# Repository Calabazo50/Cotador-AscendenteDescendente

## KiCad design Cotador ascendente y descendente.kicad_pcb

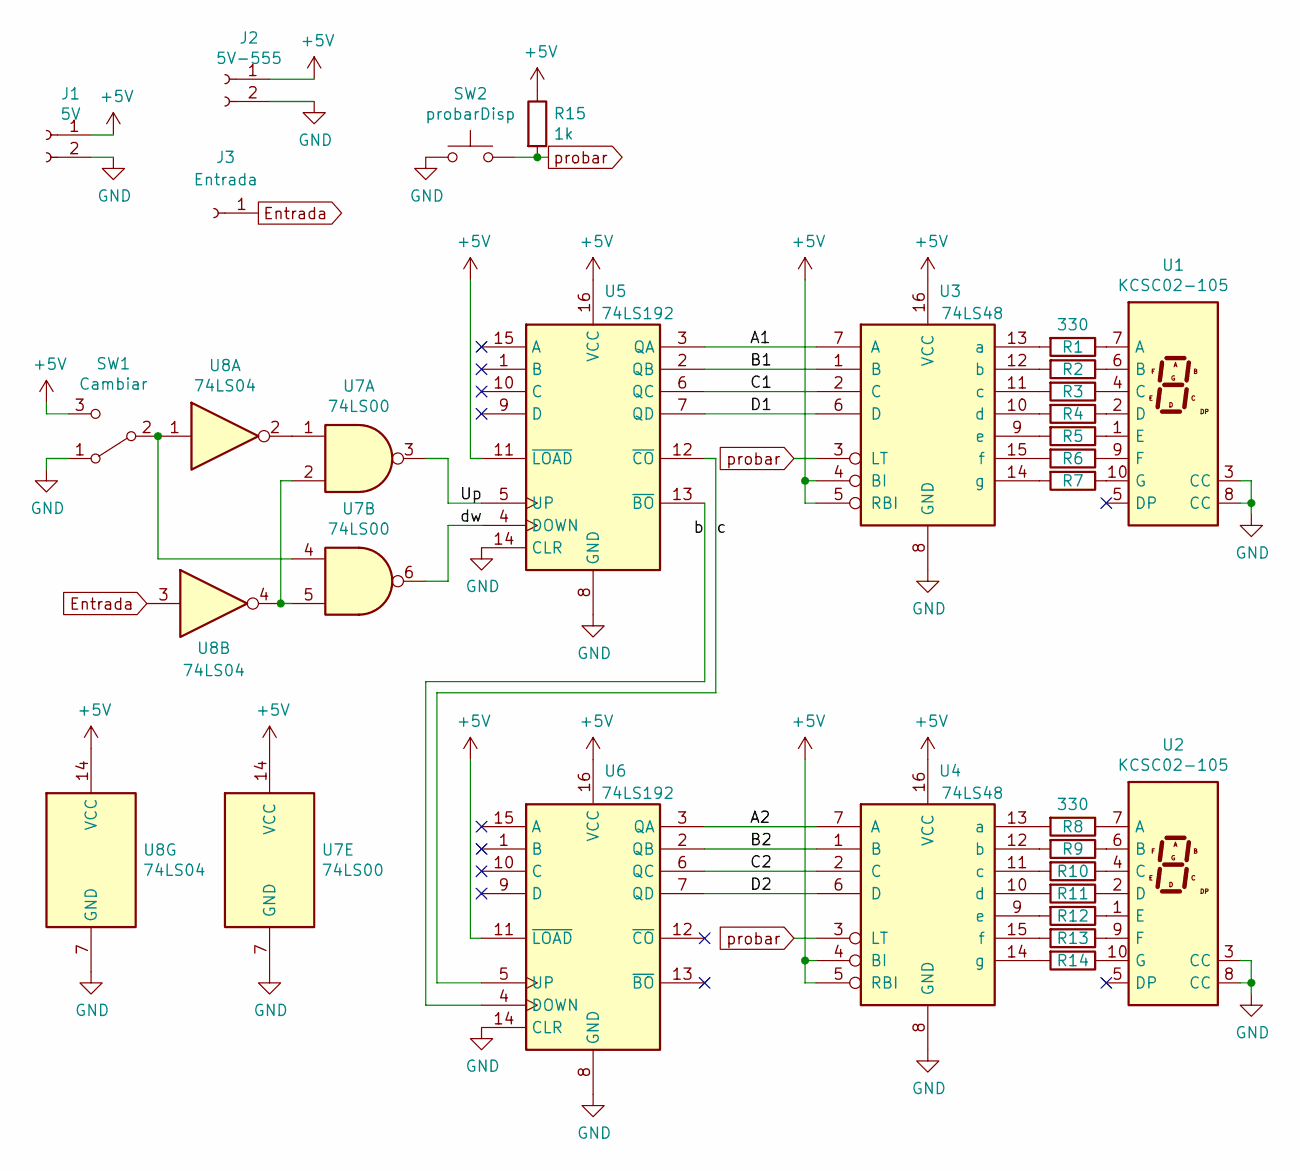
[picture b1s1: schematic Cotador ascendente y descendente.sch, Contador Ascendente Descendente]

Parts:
J1: 5V; PinSocket_1x02_P2.54mm_Vertical
J2: 5V-555; PinSocket_1x02_P2.54mm_Vertical
J3: Entrada; PinSocket_1x01_P2.54mm_Vertical
R1, R2, R3, R4, R5, R6, R7, R8, R9, R10, R11, R12, R13, R14: 330; R_Axial_DIN0207_L6.3mm_D2.5mm_P10.16mm_Horizontal
R15: 1k; R_Axial_DIN0207_L6.3mm_D2.5mm_P10.16mm_Horizontal
SW1: Cambiar; PinHeader_1x03_P2.54mm_Vertical
SW2: probarDisp; SW_PUSH_6mm
U1, U2: KCSC02-105; 7SegmentLED_LTS6760_LTS6780
U3, U4: 74LS48; DIP-16_W7.62mm_Socket_LongPads
U5, U6: 74LS192; DIP-16_W7.62mm_Socket_LongPads
U7: 74LS00; DIP-14_W7.62mm_Socket_LongPads
U8: 74LS04; DIP-14_W7.62mm_Socket_LongPads

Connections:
+5V: J1.1, J2.1, R15.1, SW1.3 (C), U3.4 (BI), U3.5 (RBI), U3.16 (VCC), U4.4 (BI), U4.5 (RBI), U4.16 (VCC), U5.11 (~LOAD), U5.16 (VCC), U6.11 (~LOAD), U6.16 (VCC), U7.14 (VCC), U8.14 (VCC)
/A1: U3.7 (A), U5.3 (QA)
/A2: U4.7 (A), U6.3 (QA)
/B1: U3.1 (B), U5.2 (QB)
/B2: U4.1 (B), U6.2 (QB)
/C1: U3.2 (C), U5.6 (QC)
/C2: U4.2 (C), U6.6 (QC)
/D1: U3.6 (D), U5.7 (QD)
/D2: U4.6 (D), U6.7 (QD)
/Up: U5.5 (UP), U7.3
/b: U5.13 (~BO), U6.4 (DOWN)
/c: U5.12 (~CO), U6.5 (UP)
/dw: U5.4 (DOWN), U7.6
Entrada: J3.1, U8.3
GND: J1.2, J2.2, SW1.1 (A), SW2.1, U1.3 (CC), U1.8 (CC), U2.3 (CC), U2.8 (CC), U3.8 (GND), U4.8 (GND), U5.8 (GND), U5.14 (CLR), U6.8 (GND), U6.14 (CLR), U7.7 (GND), U8.7 (GND)
unnamed: R1.1, U1.7 (A)
unnamed: R1.2, U3.13 (a)
unnamed: R2.1, U1.6 (B)
unnamed: R2.2, U3.12 (b)
unnamed: R3.1, U1.4 (C)
unnamed: R3.2, U3.11 (c)
unnamed: R4.1, U1.2 (D)
unnamed: R4.2, U3.10 (d)
unnamed: R5.1, U1.1 (E)
unnamed: R5.2, U3.9 (e)
unnamed: R6.1, U1.9 (F)
unnamed: R6.2, U3.15 (f)
unnamed: R7.1, U1.10 (G)
unnamed: R7.2, U3.14 (g)
unnamed: R8.1, U2.7 (A)
unnamed: R8.2, U4.13 (a)
unnamed: R9.1, U2.6 (B)
unnamed: R9.2, U4.12 (b)
unnamed: R10.1, U2.4 (C)
unnamed: R10.2, U4.11 (c)
unnamed: R11.1, U2.2 (D)
unnamed: R11.2, U4.10 (d)
unnamed: R12.1, U2.1 (E)
unnamed: R12.2, U4.9 (e)
unnamed: R13.1, U2.9 (F)
unnamed: R13.2, U4.15 (f)
unnamed: R14.1, U2.10 (G)
unnamed: R14.2, U4.14 (g)
unnamed: SW1.2 (B), U7.4, U8.1
unnamed: U7.1, U8.2
unnamed: U7.2, U7.5, U8.4
probar: R15.2, SW2.2, U3.3 (LT), U4.3 (LT)

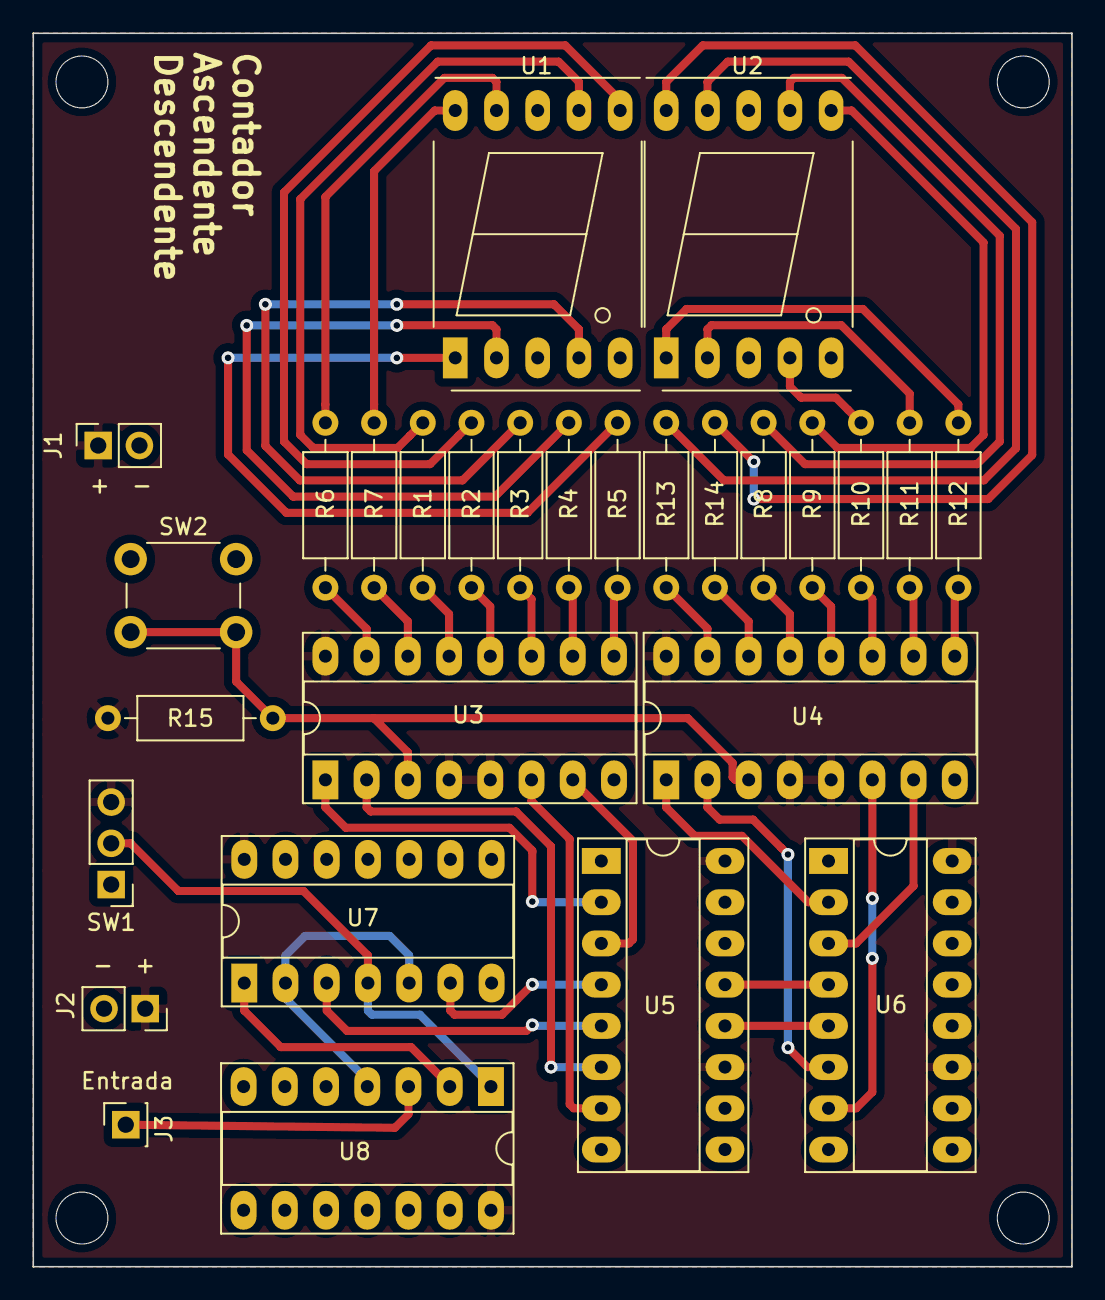
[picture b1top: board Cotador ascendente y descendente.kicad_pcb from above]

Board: 2 copper layers, 64.0 x 76.0 mm, 28 parts (0 on the bottom side), 47 nets.

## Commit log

2021-08-23 versión 1
